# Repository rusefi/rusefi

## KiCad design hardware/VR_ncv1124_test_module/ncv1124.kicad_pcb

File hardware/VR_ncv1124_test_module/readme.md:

Not suitable for crank sensor. Use this for your wheel speed or transmission shaft.

On stm32 consider using together with https://github.com/rusefi/rusefi-hardware/tree/main/frequency-divider

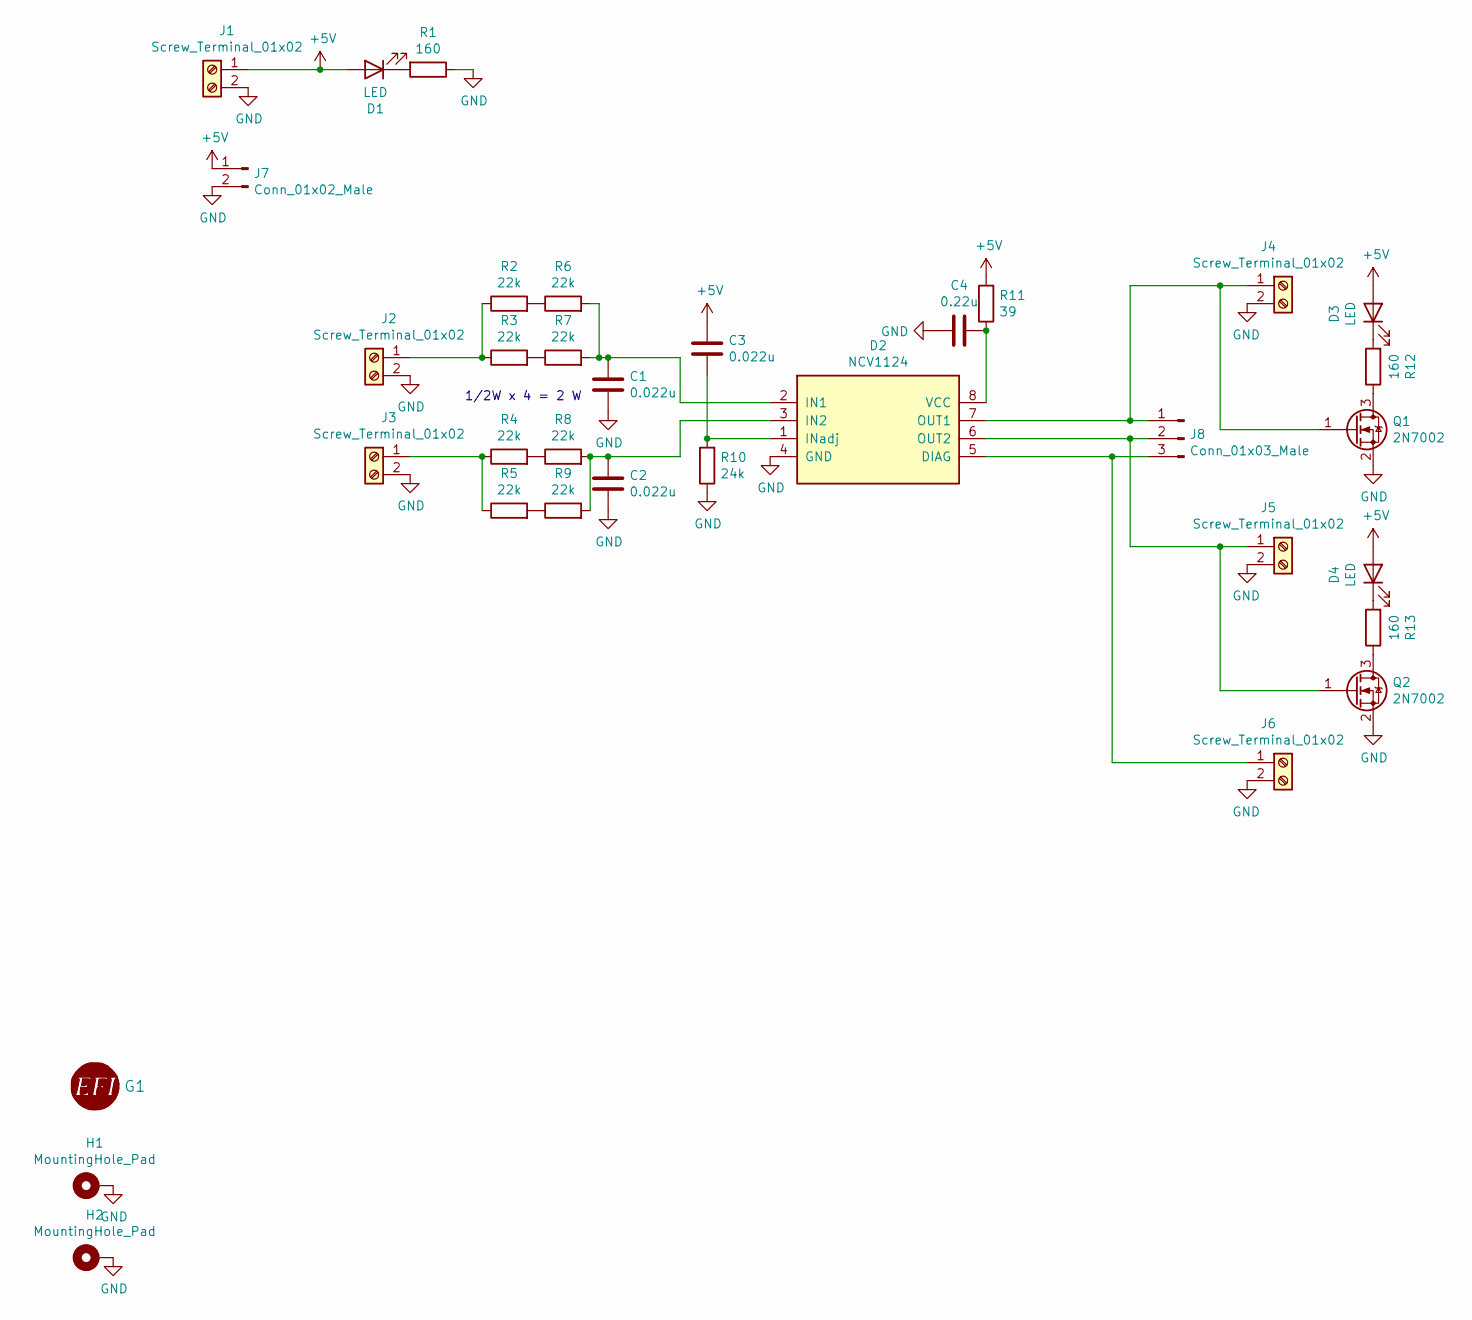
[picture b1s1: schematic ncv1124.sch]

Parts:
C1, C2, C3: 0.022u; C_1206_3216Metric_Pad1.33x1.80mm_HandSolder; LCSC C47526
C4: 0.22u; C_1206_3216Metric_Pad1.33x1.80mm_HandSolder; LCSC C1857
D1, D3, D4: LED; LED_0805_2012Metric_Pad1.15x1.40mm_HandSolder; LCSC C2296
D2: NCV1124; SO-8_3.9x4.9mm_P1.27mm; LCSC C152274
G1: LOGO
H1, H2: MountingHole_Pad; MountingHole_3.2mm_M3_Pad_Via
J1, J2, J3, J4, J5, J6: Screw_Terminal_01x02; TerminalBlock_RND_205-00001_1x02_P5.00mm_Horizontal
J7: Conn_01x02_Male; PinHeader_1x02_P2.54mm_Vertical
J8: Conn_01x03_Male; PinHeader_1x03_P2.54mm_Vertical
Q1, Q2: 2N7002; SOT-23; LCSC C8545
R1, R12, R13: 160; R_0805_2012Metric_Pad1.20x1.40mm_HandSolder; LCSC C25269
R2, R3, R4, R5, R6, R7, R8, R9: 22k; R_1210_3225Metric_Pad1.30x2.65mm_HandSolder; LCSC C147142
R10: 24k; R_1206_3216Metric_Pad1.30x1.75mm_HandSolder; LCSC C17960
R11: 39; R_1206_3216Metric_Pad1.30x1.75mm_HandSolder; LCSC C22198

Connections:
+5V: C3.1, D1.2 (A), D3.2 (A), D4.2 (A), J1.1, J7.1, R11.2
GND: C1.2, C2.2, C4.2, D2.4 (GND), H1.1, H2.1, J1.2, J2.2, J3.2, J4.2, J5.2, J6.2, J7.2, Q1.2 (S), Q2.2 (S), R1.1, R10.1; also elsewhere on the board
unnamed: C1.1, D2.2 (IN1), R6.2, R7.2
unnamed: C2.1, D2.3 (IN2), R8.2, R9.2
unnamed: C3.2, D2.1 (INadj), R10.2
unnamed: C4.1, D2.8 (VCC), R11.1
unnamed: D1.1 (K), R1.2
unnamed 7: D2.5 (DIAG), J6.1, J8.3; also elsewhere on the board
unnamed: D2.6 (OUT2), J5.1, J8.2, Q2.1 (G)
unnamed: D2.7 (OUT1), J4.1, J8.1, Q1.1 (G)
unnamed: D3.1 (K), R12.2
unnamed: D4.1 (K), R13.2
unnamed: J2.1, R2.1, R3.1
unnamed: J3.1, R4.1, R5.1
unnamed: Q1.3 (D), R12.1
unnamed: Q2.3 (D), R13.1
unnamed: R2.2, R6.1
unnamed: R3.2, R7.1
unnamed: R4.2, R8.1
unnamed: R5.2, R9.1

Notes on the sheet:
1/2W x 4 = 2 W

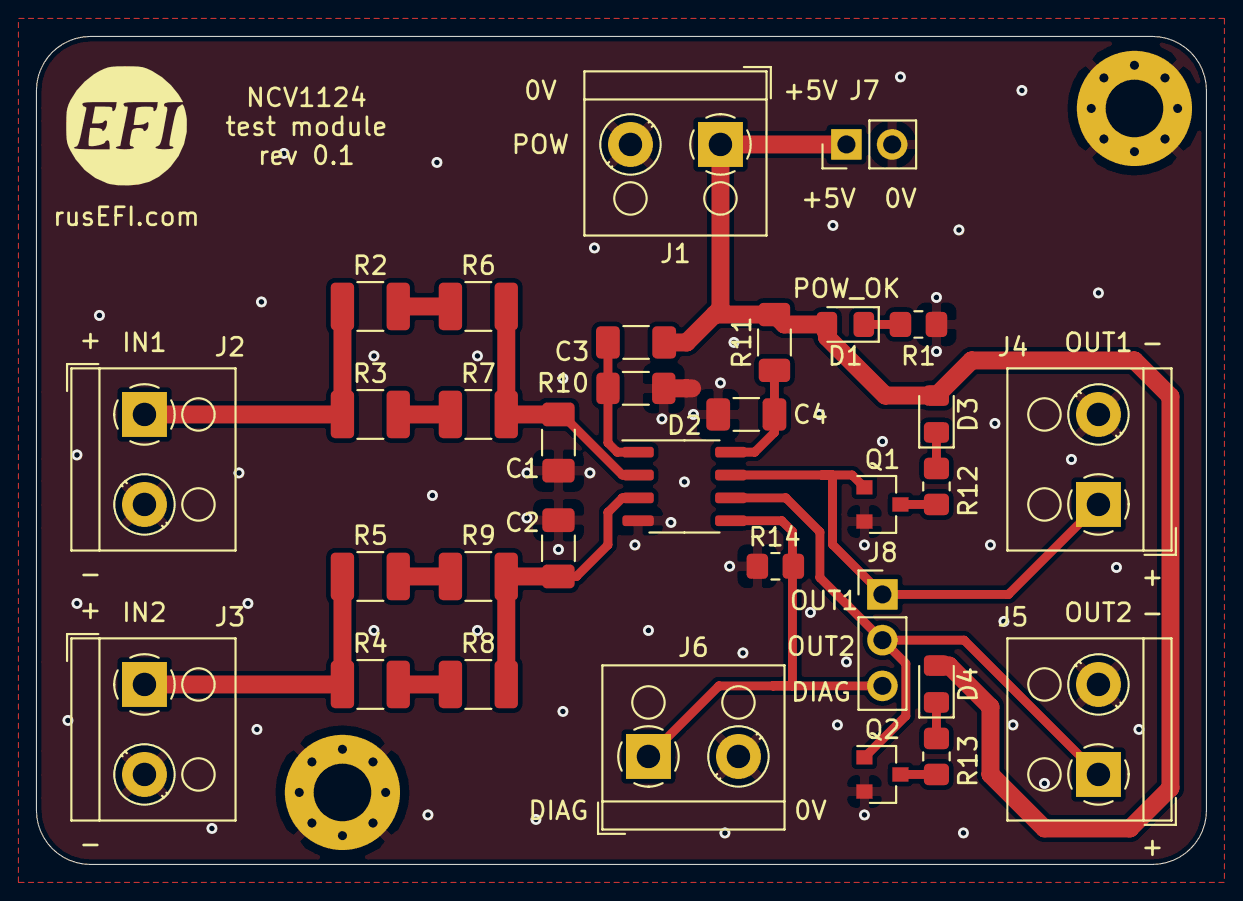
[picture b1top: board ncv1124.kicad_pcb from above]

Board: 2 copper layers, 65.0 x 46.0 mm, 35 parts (0 on the bottom side), 20 nets.

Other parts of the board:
R14: 3K; R_0805_2012Metric_Pad1.20x1.40mm_HandSolder

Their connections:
GND: R14.1; also elsewhere on the board
unnamed 7: R14.2; also elsewhere on the board

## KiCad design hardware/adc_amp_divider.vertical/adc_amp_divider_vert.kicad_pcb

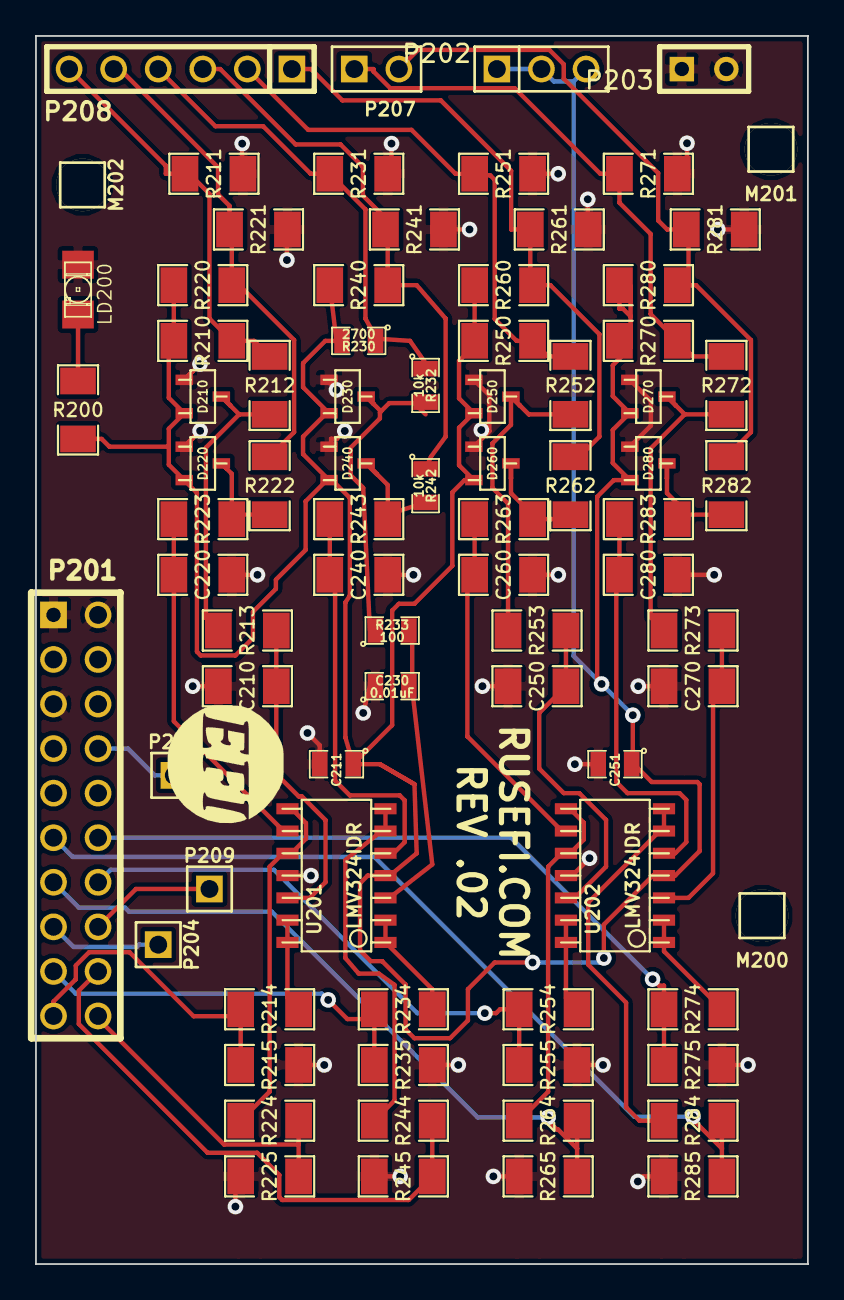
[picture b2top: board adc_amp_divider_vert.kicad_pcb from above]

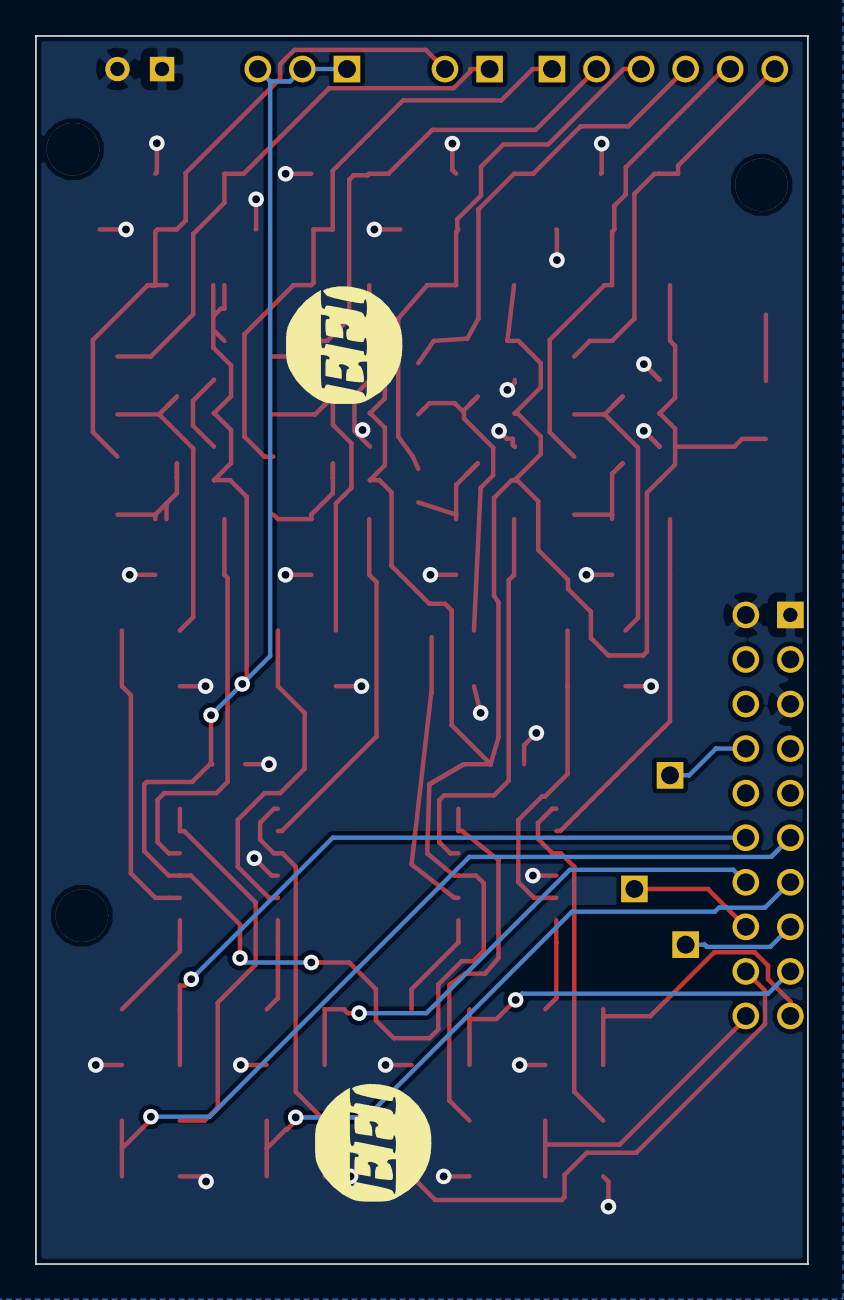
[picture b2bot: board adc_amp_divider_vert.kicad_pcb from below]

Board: 2 copper layers, 44.0 x 70.0 mm, 84 parts (2 on the bottom side), 46 nets.

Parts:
C210, C220, C240, C250, C260, C270, C280: 0.01uF; SM1206
C211, C251: 0.1uF; SM0805
C230: 0.01uF; SM0805
D210, D220, D230, D240, D250, D260, D270, D280: DOUBLE_SCHOTTKY; sot23
G200: LOGO
G201, G202: LOGO; LOGO_F
LD200: LED; LED-1206
M200, M201, M202: CONN_1; PIN_ARRAY_1
P201: CONN_10X2; PIN_ARRAY_10X2
P202: CONN_3; PIN_ARRAY_3X1
P203: CONN_2; SIL-2
P204, P205, P209: CONN_1; PIN_ARRAY_1
P207: CONN_2; PIN_ARRAY_2X1
P208: CONN_6; PIN_ARRAY-6X1
R200, R213, R223, R243, R253, R263, R273, R283: 100; SM1206
R210, R220, R240, R250, R260, R270, R280: 2700; SM1206
R211, R221, R231, R241, R251, R261, R271, R281: 500K; SM1206
R212, R222, R252, R262, R272, R282: 10k; SM1206
R214, R215, R224, R225, R234, R235, R244, R245, R254, R255, R264, R265, R274, R275, R284, R285: 1500; SM1206
R230: 2700; SM0805
R232, R242: 10k; SM0805
R233: 100; SM0805
U201, U202: LMV324IDR; so-14

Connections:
/5V: C211.1, C251.1, D210.3, D220.3, D230.3, D240.3, D250.3, D260.3, D270.3, D280.3, P202.1, P202.2, P202.3, R200.1, R210.2, R220.2, R230.2, R240.2, R250.2, R260.2, R270.2, R280.2, U201.4, U202.4
/INP1: P208.6, R210.1, R211.1, R212.1
/INP2: P208.5, R220.1, R221.1, R222.1
/INP3: P208.4, R230.1, R231.1, R232.1
/INP4: P208.3, R240.1, R241.1, R242.1
/INP5: P208.2, R250.1, R251.1, R252.1
/INP6: P208.1, R260.1, R261.1, R262.1
/INP7: P207.1, R270.1, R271.1, R272.1
/INP8: P207.2, R280.1, R281.1, R282.1
/OUT1: P201.19, R214.2, R215.1
/OUT2: P201.20, R224.2, R225.1
/OUT3: P201.17, R234.2, R235.1
/OUT4: P201.18, R244.2, R245.1
/OUT5: P201.14, R254.2, R255.1
/OUT6: P201.13, R264.2, R265.1
/OUT7: P201.12, R274.2, R275.1
/OUT8: P201.11, R284.2, R285.1
/PA4: P201.16, P209.1
/PA5: P201.15, P204.1
/PC0: P201.8, P205.1
GND: C210.1, C211.2, C220.1, C230.1, C240.1, C250.1, C251.2, C260.1, C270.1, C280.1, D210.1, D220.1, D230.1, D240.1, D250.1, D260.1, D270.1, D280.1, LD200.1, P201.1, P201.2, P201.5, P203.1, P203.2, R211.2, R215.2, R221.2, R225.2, R231.2, R235.2, R241.2, R245.2, R251.2, R255.2, R261.2, R265.2, R271.2, R275.2, R281.2, R285.2, U201.11, U202.11
unnamed: D240.2, R242.2, R243.1
unnamed: D220.2, R222.2, R223.1
unnamed: D250.2, R252.2, R253.1
unnamed: D260.2, R262.2, R263.1
unnamed: D210.2, R212.2, R213.1
unnamed: C280.2, R283.2, U202.5
unnamed: C270.2, R273.2, U202.3
unnamed: R284.1, U202.6, U202.7
unnamed: R274.1, U202.1, U202.2
unnamed: C240.2, R243.2, U201.5
unnamed: LD200.2, R200.2
unnamed: C260.2, R263.2, U202.9
unnamed: C250.2, R253.2, U202.12
unnamed: R264.1, U202.8, U202.10
unnamed: R254.1, U202.13, U202.14
unnamed: D270.2, R272.2, R273.1
unnamed: D280.2, R282.2, R283.1
unnamed: R244.1, U201.6, U201.7
unnamed: R234.1, U201.1, U201.2
unnamed: R224.1, U201.8, U201.10
unnamed: C220.2, R223.2, U201.9
unnamed: C210.2, R213.2, U201.12
unnamed: C230.2, R233.2, U201.3
unnamed: R214.1, U201.13, U201.14
unnamed: D230.2, R232.2, R233.1

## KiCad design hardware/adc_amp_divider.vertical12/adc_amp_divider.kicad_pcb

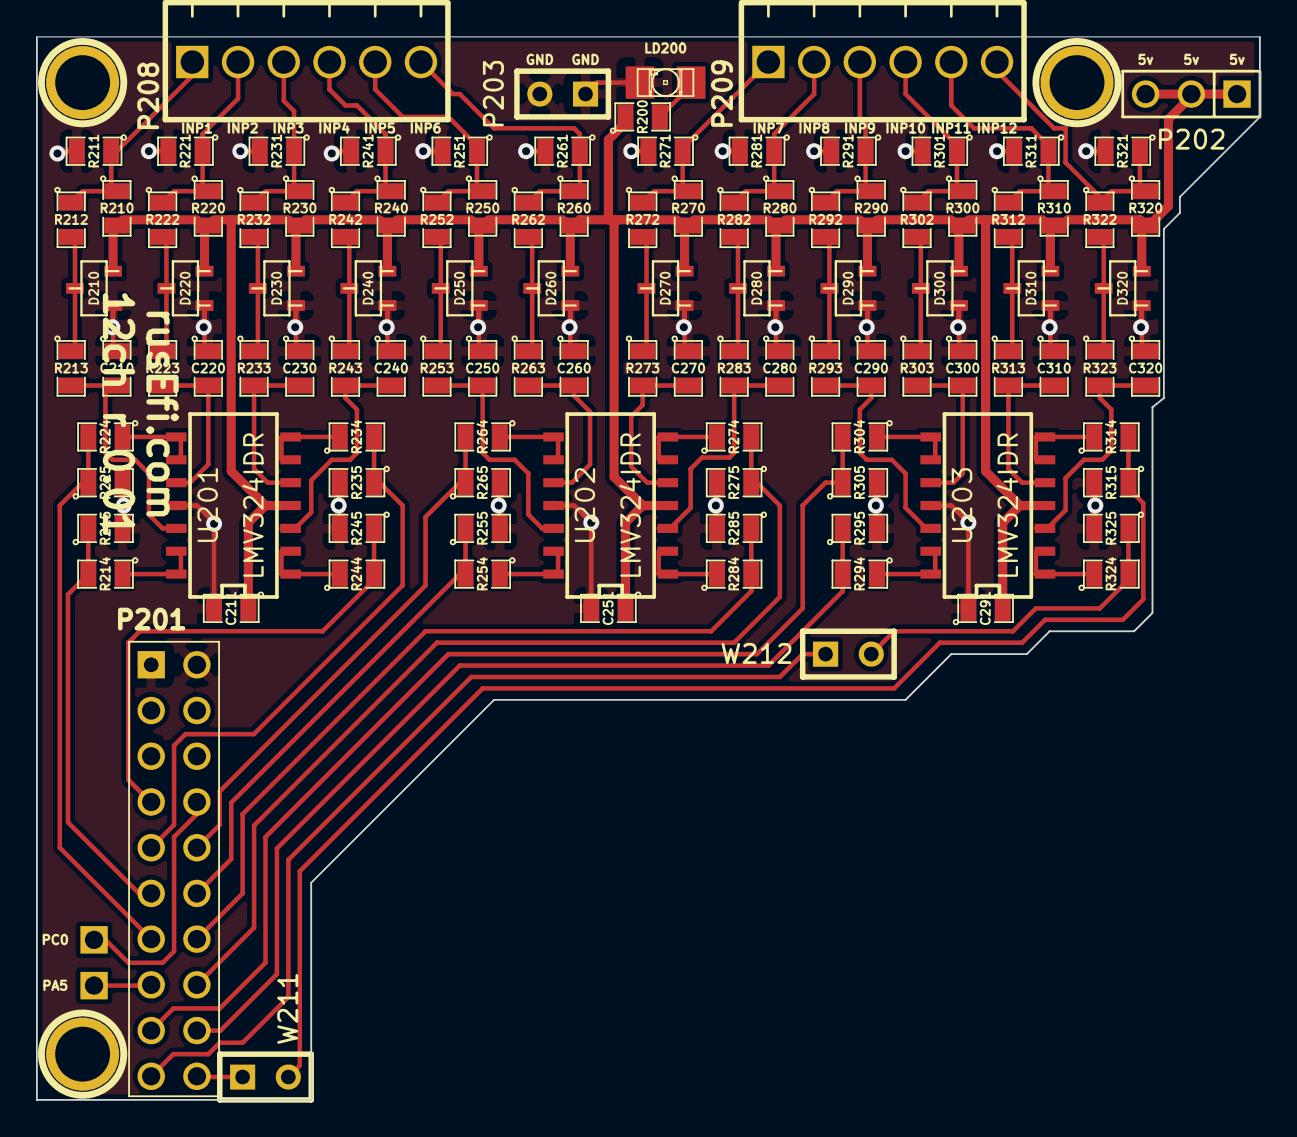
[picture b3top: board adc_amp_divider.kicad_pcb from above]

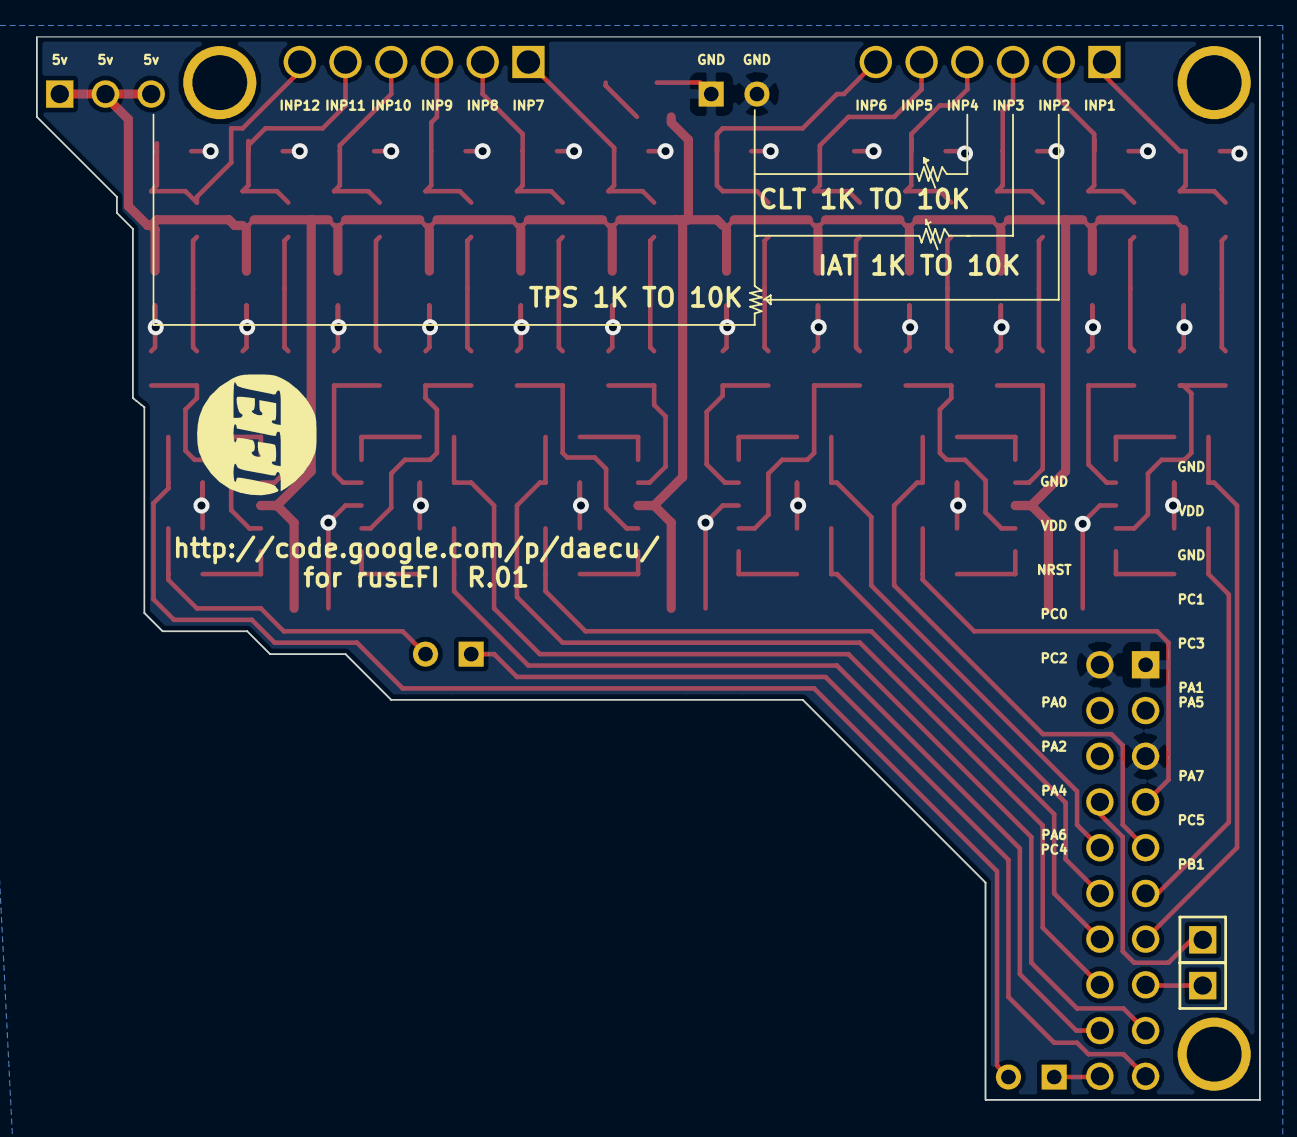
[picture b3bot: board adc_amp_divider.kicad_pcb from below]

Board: 2 copper layers, 67.9 x 59.1 mm, 117 parts (3 on the bottom side), 67 nets.

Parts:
C210, C220, C230, C240, C250, C260, C270, C280, C290, C300, C310, C320: 0.01uF; SM0805
C211, C251, C291: 0.1uF; SM0805
D210, D220, D230, D240, D250, D260, D270, D280, D290, D300, D310, D320: DOUBLE_SCHOTTKY; sot23
G201: LOGO; LOGO_F
LD200: LED; LED-1206
M200, M201, M202: CONN_1; 1pin
P201: CONN_10X2; PIN_ARRAY_10X2_M
P202: CONN_3; PIN_ARRAY_3X1
P203: CONN_2; SIL-2
P204, P205: CONN_1; PIN_ARRAY_1
P208, P209: CONN_6; 6_screw_term_.1in
R200, R213, R223, R233, R243, R253, R263, R273, R283, R293, R303, R313, R323: 100; SM0805
R210, R220, R230, R240, R250, R260, R270, R280, R290, R300, R310, R320: 2700; SM0805
R211, R221, R231, R241, R251, R261, R271, R281, R291, R301, R311, R321: 500K; SM0805
R212, R222, R232, R242, R252, R262, R272, R282, R292, R302, R312, R322: 10k; SM0805
R214, R215, R224, R225, R234, R235, R244, R245, R254, R255, R264, R265, R274, R275, R284, R285, R294, R295, R304, R305, R314, R315, R324, R325: 1500; SM0805
U201, U202, U203: LMV324IDR; SO14N
W211, W212: TEST; SIL-2

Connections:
/5V: C211.1, C251.1, C291.2, D210.3, D220.3, D230.3, D240.3, D250.3, D260.3, D270.3, D280.3, D290.3, D300.3, D310.3, D320.3, P202.1, P202.2, P202.3, R200.1, R210.2, R220.2, R230.2, R240.2, R250.2, R260.2, R270.2, R280.2, R290.2, R300.2, R310.2, R320.2, U201.4, U202.4, U203.4
/INP1: P208.1, R210.1, R211.1, R212.1
/INP2: P208.2, R220.1, R221.1, R222.1
/INP3: P208.3, R230.1, R231.1, R232.1
/INP4: P208.4, R240.1, R241.1, R242.1
/INP5: P208.5, R250.1, R251.1, R252.1
/INP6: P208.6, R260.1, R261.1, R262.1
/INP7: P209.1, R270.1, R271.1, R272.1
/INP8: P209.2, R280.1, R281.1, R282.1
/INP9: P209.3, R290.1, R291.1, R292.1
/INP10: P209.4, R300.1, R301.1, R302.1
/INP11: P209.5, R310.1, R311.1, R312.1
/INP12: P209.6, R320.1, R321.1, R322.1
/OUT1: P201.11, R214.2, R215.1
/OUT2: P201.13, R224.2, R225.1
/OUT3: P201.9, R234.2, R235.1
/OUT4: P201.7, R244.2, R245.1
/OUT5: P201.12, R254.2, R255.1
/OUT6: P201.10, R264.2, R265.1
/OUT7: P201.16, R274.2, R275.1
/OUT8: P201.14, R284.2, R285.1
/OUT9: P201.18, R294.2, R295.1
/OUT10: P201.17, R304.2, R305.1
/OUT11: P201.20, W211.1
/OUT12: P201.19, W212.1
/PA5: P201.15, P204.1
/PC0: P201.8, P205.1
GND: C210.1, C211.2, C220.1, C230.1, C240.1, C250.1, C251.2, C260.1, C270.1, C280.1, C290.1, C291.1, C300.1, C310.1, C320.1, D210.1, D220.1, D230.1, D240.1, D250.1, D260.1, D270.1, D280.1, D290.1, D300.1, D310.1, D320.1, LD200.2, P201.1, P201.2, P201.5, P203.1, P203.2, R211.2, R215.2, R221.2, R225.2, R231.2, R235.2, R241.2, R245.2, R251.2, R255.2, R261.2, R265.2, R271.2, R275.2, R281.2, R285.2, R291.2, R295.2, R301.2, R305.2, R311.2, R315.2, R321.2, R325.2, U201.11, U202.11, U203.11
unnamed: D250.2, R252.2, R253.1
unnamed: D260.2, R262.2, R263.1
unnamed: D210.2, R212.2, R213.1
unnamed: D220.2, R222.2, R223.1
unnamed: D280.2, R282.2, R283.1
unnamed: R214.1, U201.13, U201.14
unnamed: R224.1, U201.8, U201.9
unnamed: D270.2, R272.2, R273.1
unnamed: R244.1, U201.1, U201.2
unnamed: D300.2, R302.2, R303.1
unnamed: D290.2, R292.2, R293.1
unnamed: R304.1, U203.8, U203.9
unnamed: R294.1, U203.13, U203.14
unnamed: C290.2, R293.2, U203.12
unnamed: C300.2, R303.2, U203.10
unnamed: R314.1, U203.6, U203.7
unnamed: R324.1, U203.1, U203.2
unnamed: C310.2, R313.2, U203.5
unnamed: C320.2, R323.2, U203.3
unnamed: D320.2, R322.2, R323.1
unnamed: D310.2, R312.2, R313.1
unnamed: R324.2, R325.1, W212.2
unnamed: R314.2, R315.1, W211.2
unnamed: C250.2, R253.2, U202.12
unnamed: R254.1, U202.13, U202.14
unnamed: R274.1, U202.6, U202.7
unnamed: R264.1, U202.8, U202.9
unnamed: C240.2, R243.2, U201.3
unnamed: C230.2, R233.2, U201.5
unnamed: C270.2, R273.2, U202.5
unnamed: C280.2, R283.2, U202.3
unnamed: C220.2, R223.2, U201.10
unnamed: C210.2, R213.2, U201.12
unnamed: C260.2, R263.2, U202.10
unnamed: R284.1, U202.1, U202.2
unnamed: D240.2, R242.2, R243.1
unnamed: LD200.1, R200.2
unnamed: D230.2, R232.2, R233.1
unnamed: R234.1, U201.6, U201.7

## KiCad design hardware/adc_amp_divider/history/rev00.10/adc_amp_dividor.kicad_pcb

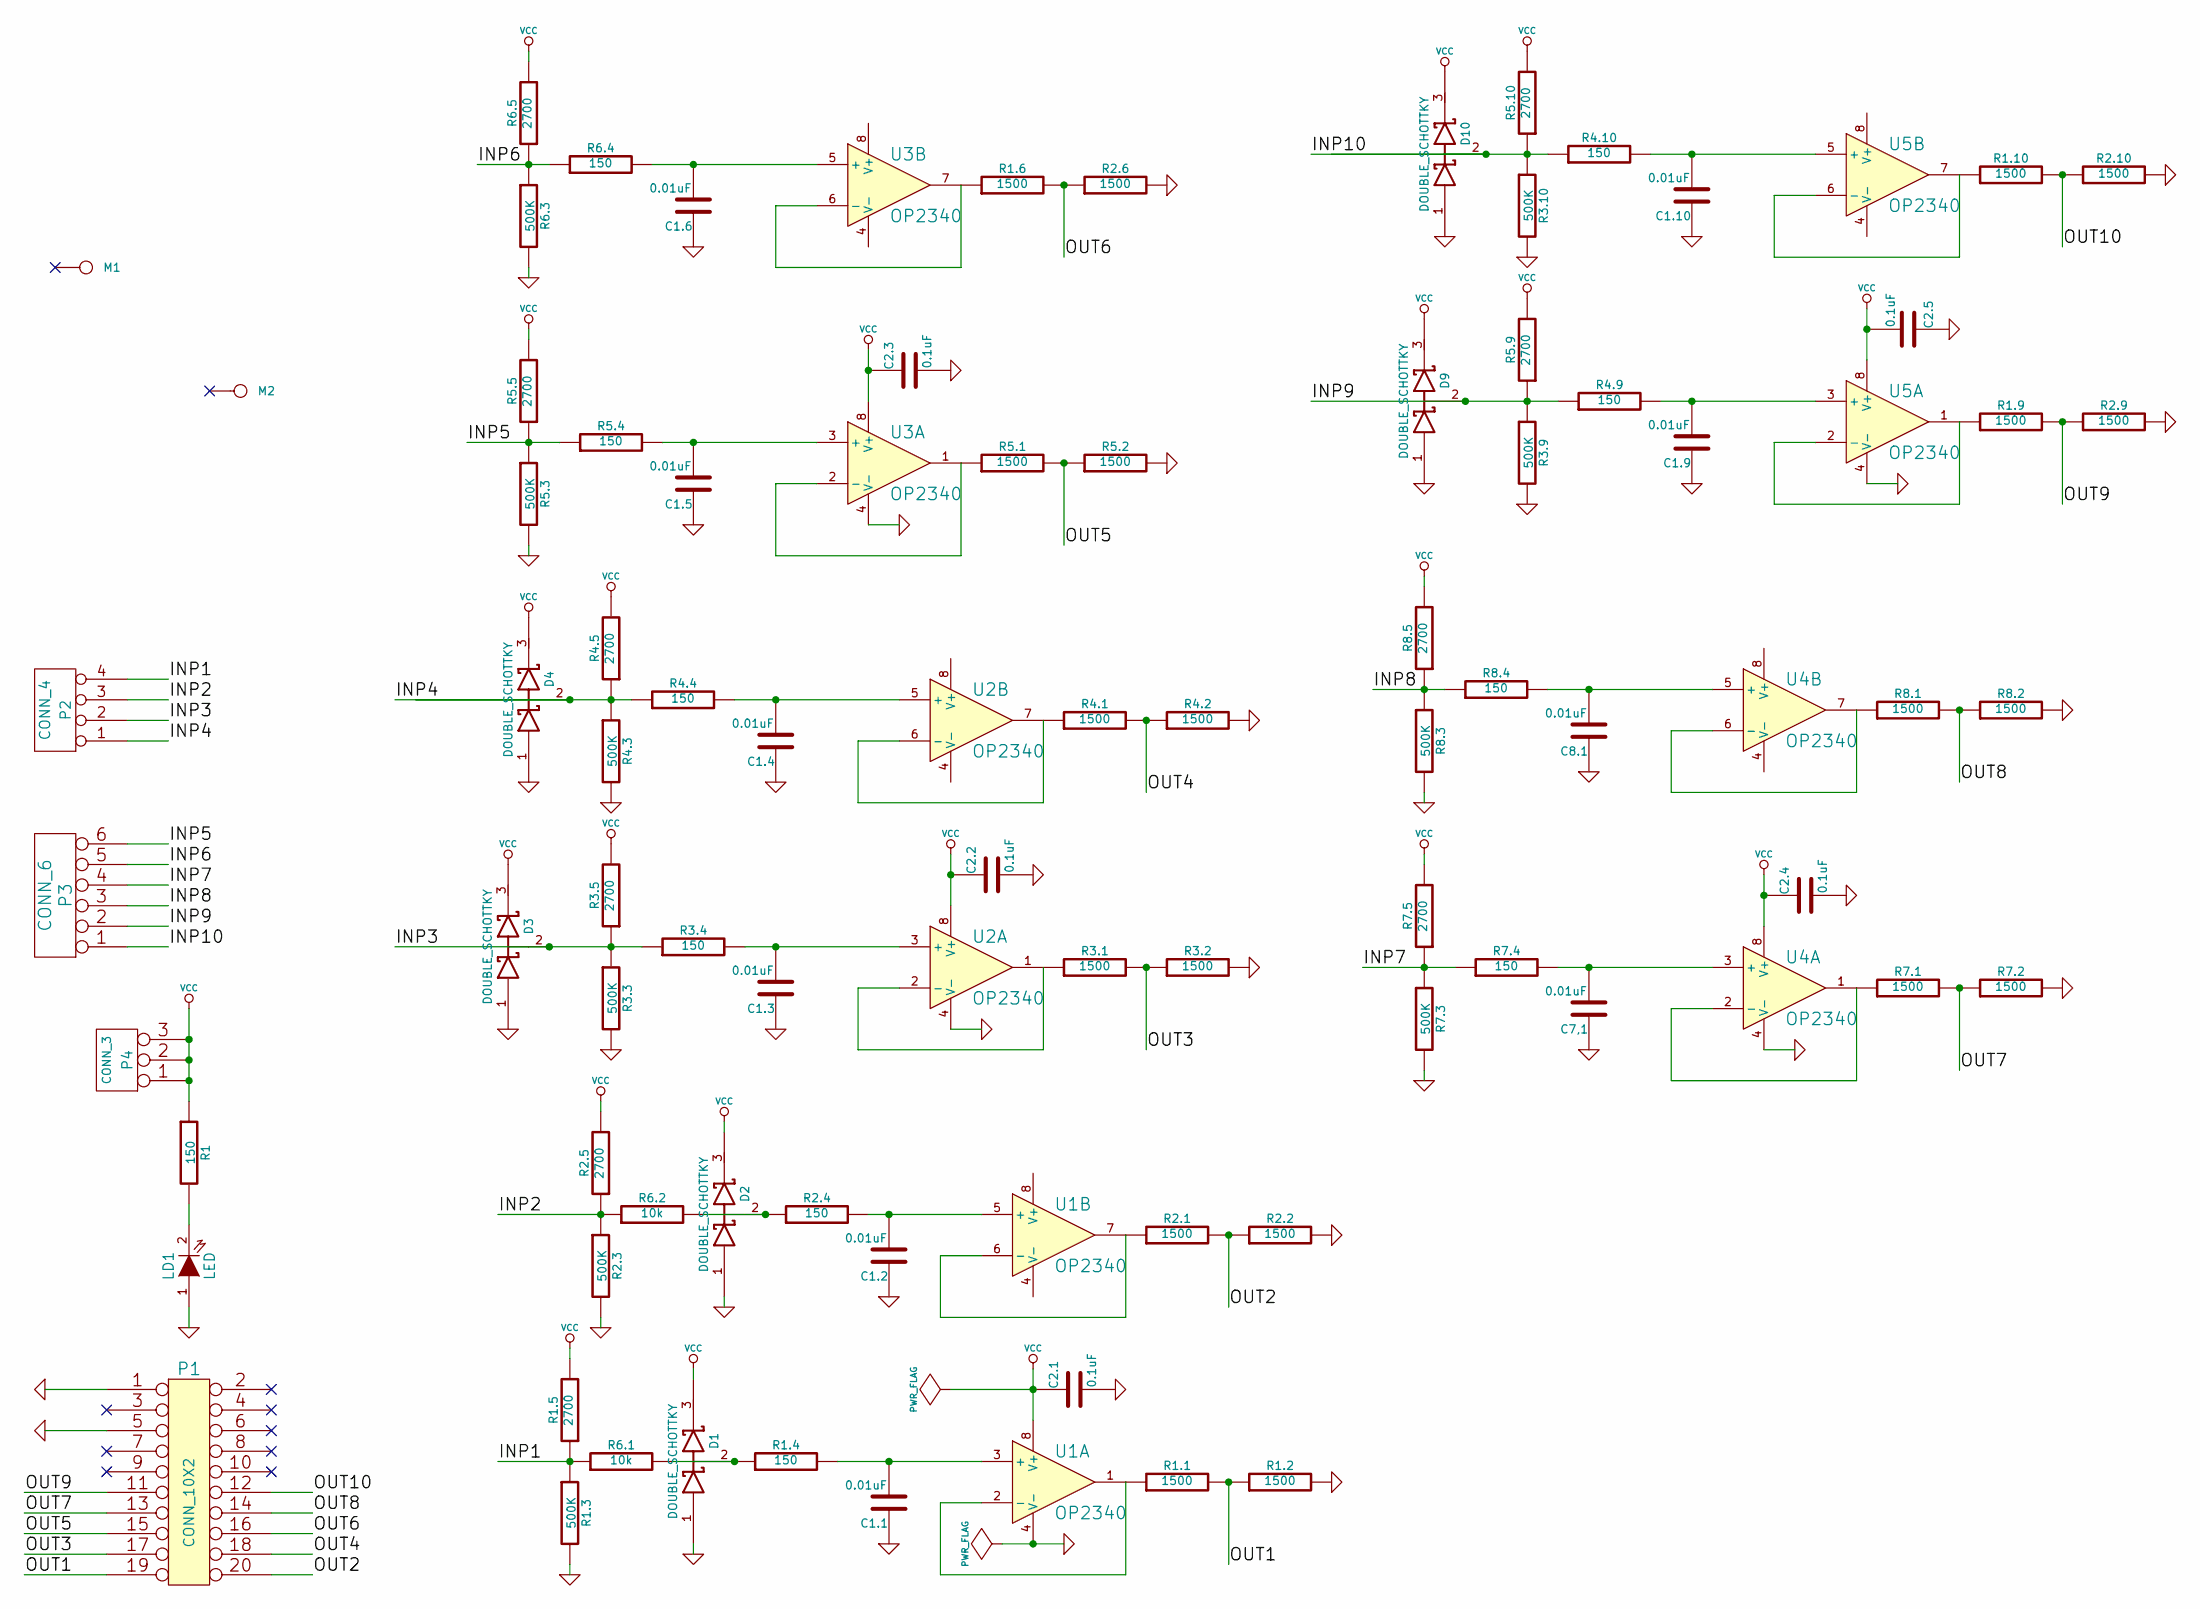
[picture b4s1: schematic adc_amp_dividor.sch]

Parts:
C1.1, C1.2, C1.3, C1.4, C1.5, C1.6, C1.9, C1.10, C7,1, C8.1: 0.01uF
C2.1, C2.2, C2.3, C2.4, C2.5: 0.1uF
D1, D2, D3, D4, D9, D10: DOUBLE_SCHOTTKY
LD1: LED
M1, M2: CONN_1
P1: CONN_10X2
P2: CONN_4
P3: CONN_6
P4: CONN_3
R1, R1.4, R2.4, R3.4, R4.4, R4.9, R4.10, R5.4, R6.4, R7.4, R8.4: 150
R1.1, R1.2, R1.6, R1.9, R1.10, R2.1, R2.2, R2.6, R2.9, R2.10, R3.1, R3.2, R4.1, R4.2, R5.1, R5.2, R7.1, R7.2, R8.1, R8.2: 1500
R1.3, R2.3, R3.3, R3.9, R3.10, R4.3, R5.3, R6.3, R7.3, R8.3: 500K
R1.5, R2.5, R3.5, R4.5, R5.5, R5.9, R5.10, R6.5, R7.5, R8.5: 2700
R6.1, R6.2: 10k
U1, U2, U3, U4, U5: OP2340

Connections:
/INP1: P2.4, R1.3.1, R1.5.1, R6.1.1
/INP2: P2.3, R2.3.1, R2.5.1, R6.2.1
/INP3: D3.2 (AK), P2.2, R3.3.1, R3.4.1, R3.5.1
/INP4: D4.2 (AK), P2.1, R4.3.1, R4.4.1, R4.5.1
/INP5: P3.6, R5.3.1, R5.4.1, R5.5.1
/INP6: P3.5, R6.3.1, R6.4.1, R6.5.1
/INP7: P3.4, R7.3.1, R7.4.1, R7.5.1
/INP8: P3.3, R8.3.1, R8.4.1, R8.5.1
/INP9: D9.2 (AK), P3.2, R3.9.1, R4.9.1, R5.9.1
/INP10: D10.2 (AK), P3.1, R3.10.1, R4.10.1, R5.10.1
/OUT1: P1.19, R1.1.2, R1.2.1
/OUT2: P1.20, R2.1.2, R2.2.1
/OUT3: P1.17, R3.1.2, R3.2.1
/OUT4: P1.18, R4.1.2, R4.2.1
/OUT5: P1.15, R5.1.2, R5.2.1
/OUT6: P1.16, R1.6.2, R2.6.1
/OUT7: P1.13, R7.1.2, R7.2.1
/OUT8: P1.14, R8.1.2, R8.2.1
/OUT9: P1.11, R1.9.2, R2.9.1
/OUT10: P1.12, R1.10.2, R2.10.1
GND: C1.1.1, C1.2.1, C1.3.1, C1.4.1, C1.5.1, C1.6.1, C1.9.1, C1.10.1, C2.1.2, C2.2.2, C2.3.2, C2.4.2, C2.5.1, C7,1.1, C8.1.1, D1.1 (Anode), D2.1 (Anode), D3.1 (Anode), D4.1 (Anode), D9.1 (Anode), D10.1 (Anode), LD1.1 (A), P1.1, P1.5, R1.2.2, R1.3.2, R2.2.2, R2.3.2, R2.6.2, R2.9.2, R2.10.2, R3.2.2, R3.3.2, R3.9.2, R3.10.2, R4.2.2, R4.3.2, R5.2.2, R5.3.2, R6.3.2, R7.2.2, R7.3.2, R8.2.2, R8.3.2, U1.4 (V-), U2.4 (V-), U3.4 (V-), U4.4 (V-), U5.4 (V-)
unnamed: LD1.2 (K), R1.2
unnamed: R5.1.1, U3.1, U3.2 (-)
unnamed: R1.6.1, U3.6 (-), U3.7
unnamed: R3.1.1, U2.1, U2.2 (-)
unnamed: R4.1.1, U2.6 (-), U2.7
unnamed: R2.1.1, U1.6 (-), U1.7
unnamed: R1.1.1, U1.1, U1.2 (-)
unnamed: R7.1.1, U4.1, U4.2 (-)
unnamed: R8.1.1, U4.6 (-), U4.7
unnamed: R1.9.1, U5.1, U5.2 (-)
unnamed: R1.10.1, U5.6 (-), U5.7
unnamed: C1.10.2, R4.10.2, U5.5 (+)
unnamed: D2.2 (AK), R2.4.1, R6.2.2
unnamed: D1.2 (AK), R1.4.1, R6.1.2
unnamed: C1.9.2, R4.9.2, U5.3 (+)
unnamed: C1.2.2, R2.4.2, U1.5 (+)
unnamed: C1.1.2, R1.4.2, U1.3 (+)
unnamed: C1.3.2, R3.4.2, U2.3 (+)
unnamed: C1.5.2, R5.4.2, U3.3 (+)
unnamed: C1.6.2, R6.4.2, U3.5 (+)
unnamed: C1.4.2, R4.4.2, U2.5 (+)
unnamed: C7,1.2, R7.4.2, U4.3 (+)
unnamed: C8.1.2, R8.4.2, U4.5 (+)
VCC: C2.1.1, C2.2.1, C2.3.1, C2.4.1, C2.5.2, D1.3 (cathode), D2.3 (cathode), D3.3 (cathode), D4.3 (cathode), D9.3 (cathode), D10.3 (cathode), P4.1, P4.2 (PM), P4.3, R1.1, R1.5.2, R2.5.2, R3.5.2, R4.5.2, R5.5.2, R5.9.2, R5.10.2, R6.5.2, R7.5.2, R8.5.2, U1.8 (V+), U2.8 (V+), U3.8 (V+), U4.8 (V+), U5.8 (V+)

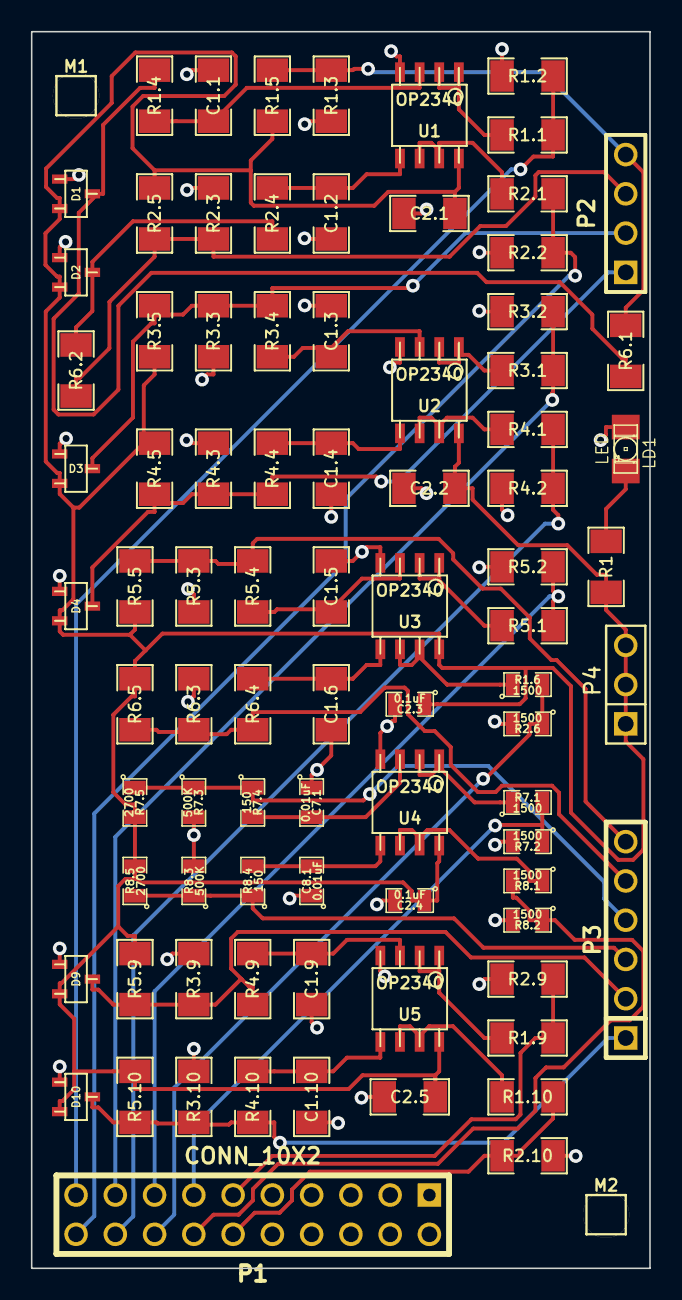
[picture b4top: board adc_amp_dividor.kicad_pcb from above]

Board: 2 copper layers, 40.0 x 80.0 mm, 86 parts (0 on the bottom side), 45 nets.
